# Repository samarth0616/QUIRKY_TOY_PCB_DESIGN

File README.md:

# QUIRKY_TOY_PCB_DESIGN
DURING MY SEMESTER BREAK I LEARNT HOW TO DESIGN MY OWN PCB BOARD AND EXPERIMENTED MY LEARNING BY MAKING A TOY OF MY OWN.
# Quirky Toy PCB 🎮

A fun toy PCB designed during my semester break to practice schematic design, PCB layout, and fabrication-ready outputs.

## 🔧 Features
- Compact toy PCB design  
- Simple logic
- buzzer interaction  
- Beginner-friendly PCB layout  

## 🛠 Tools Used
- KiCad (Schematic + PCB)
- Basic electronics components
- GitHub for version control

## 📂 Files Included
- Schematic (PDF)
- PCB Layout
- Gerber Files
- BOM
- 3D PCB Renders

## 🚀 Future Improvements
- Add sound effects  
- Improve layout compactness  
- Add enclosure

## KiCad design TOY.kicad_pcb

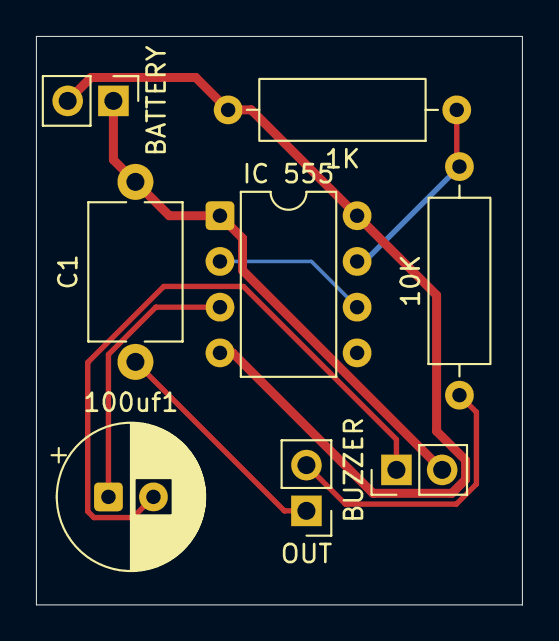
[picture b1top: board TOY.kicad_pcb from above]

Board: 2 copper layers, 27.0 x 31.6 mm, 8 parts (0 on the bottom side), 8 nets.

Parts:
1K: 1k; R_Axial_DIN0309_L9.0mm_D3.2mm_P12.70mm_Horizontal
10K: 10k; R_Axial_DIN0309_L9.0mm_D3.2mm_P12.70mm_Horizontal
100uf1: C_Polarized; CP_Radial_D8.0mm_P2.50mm
BATTERY: Battery; PinHeader_1x02_P2.54mm_Vertical
BUZZER: buzzer; PinHeader_1x02_P2.54mm_Vertical
C1: 1nf; C_Disc_D7.5mm_W5.0mm_P10.00mm
IC 555: NA555P; DIP-8_W7.62mm
OUT: human interaction; PinHeader_1x02_P2.54mm_Vertical

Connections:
/DIS: 1K.1, 10K.2, IC 555.7 (DISCH)
/OUT: 100uf1.1, IC 555.3 (OUT)
/TR: C1.1, OUT.1
GND: BATTERY.1, BUZZER.2, C1.2, IC 555.1 (GND)
unnamed: 100uf1.2, BUZZER.1
unnamed: 10K.1, OUT.2
unnamed: IC 555.2 (TRIG), IC 555.6 (THRES)
VCC: 1K.2, BATTERY.2, IC 555.4 (~RST), IC 555.8 (VCC)

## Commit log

2026-01-22 Enhance README with project overview and details
    Expanded README with project details, features, tools used, files included, and future improvements.
